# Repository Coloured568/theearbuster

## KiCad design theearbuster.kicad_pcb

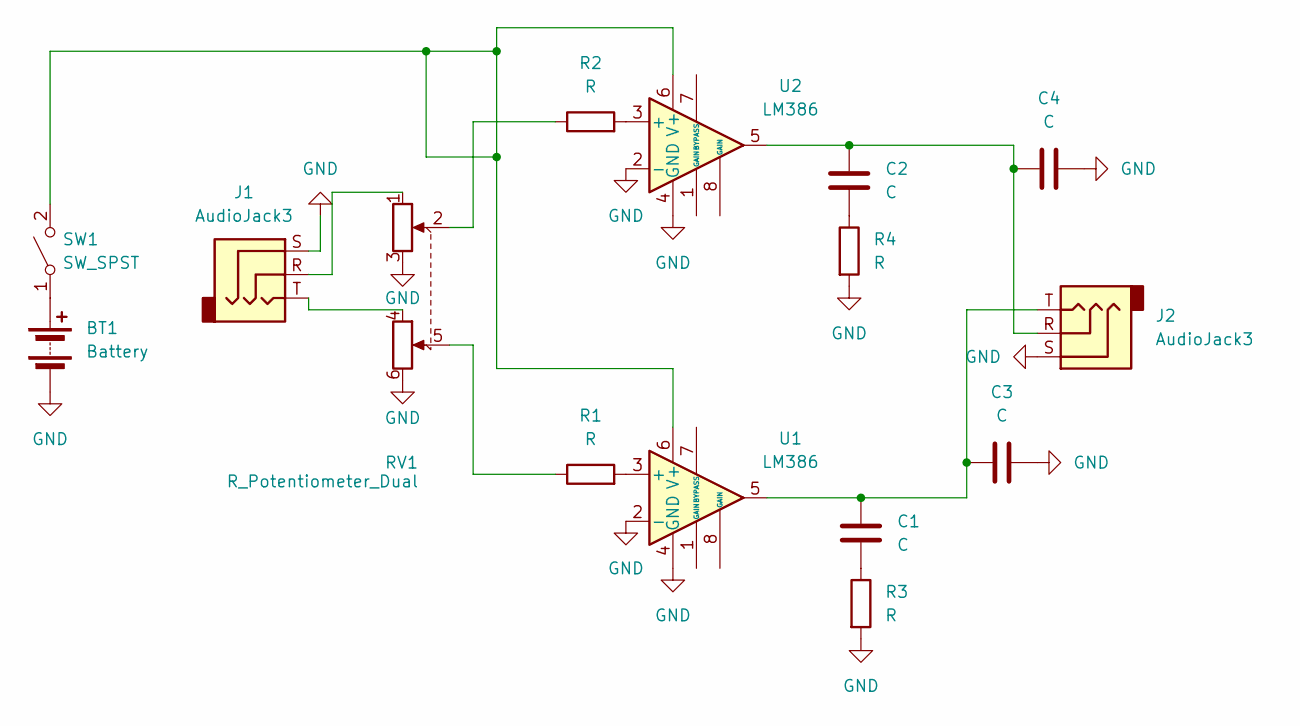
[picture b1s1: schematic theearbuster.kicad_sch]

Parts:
BT1: Battery; BatteryHolder_MPD_BA9VPC_1xPP3
C1, C2: C; C_Rect_L9.0mm_W6.7mm_P7.50mm_MKT
C3, C4: C; CP_Axial_L21.0mm_D8.0mm_P28.00mm_Horizontal
J1, J2: AudioJack3; Jack_3.5mm_PJ320D_Horizontal
R1, R2, R3, R4: R; R_Axial_DIN0204_L3.6mm_D1.6mm_P1.90mm_Vertical
RV1: R_Potentiometer_Dual; Potentiometer_Bourns_PTV112-4_Dual_Vertical
SW1: SW_SPST; SW_DIP_SPSTx01_Slide_6.7x4.1mm_W7.62mm_P2.54mm_LowProfile
U1, U2: LM386; DIP-8_W7.62mm

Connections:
GND: BT1.2 (-), C3.1, C4.1, J1.S, J2.S, R3.2, R4.2, RV1.3, RV1.6, U1.2 (-), U1.4 (GND), U2.2 (-), U2.4 (GND)
unnamed: BT1.1 (+), SW1.1 (A)
unnamed: C1.1, C3.2, J2.T, U1.5
unnamed: C1.2, R3.1
unnamed: C2.1, C4.2, J2.R, U2.5
unnamed: C2.2, R4.1
unnamed: J1.R, RV1.1
unnamed: J1.T, RV1.4
unnamed: R1.1, RV1.5
unnamed: R2.1, RV1.2
unnamed: SW1.2 (B), U1.6 (V+), U2.6 (V+)
unnamed: R1.2, U1.3 (+)
unnamed: R2.2, U2.3 (+)

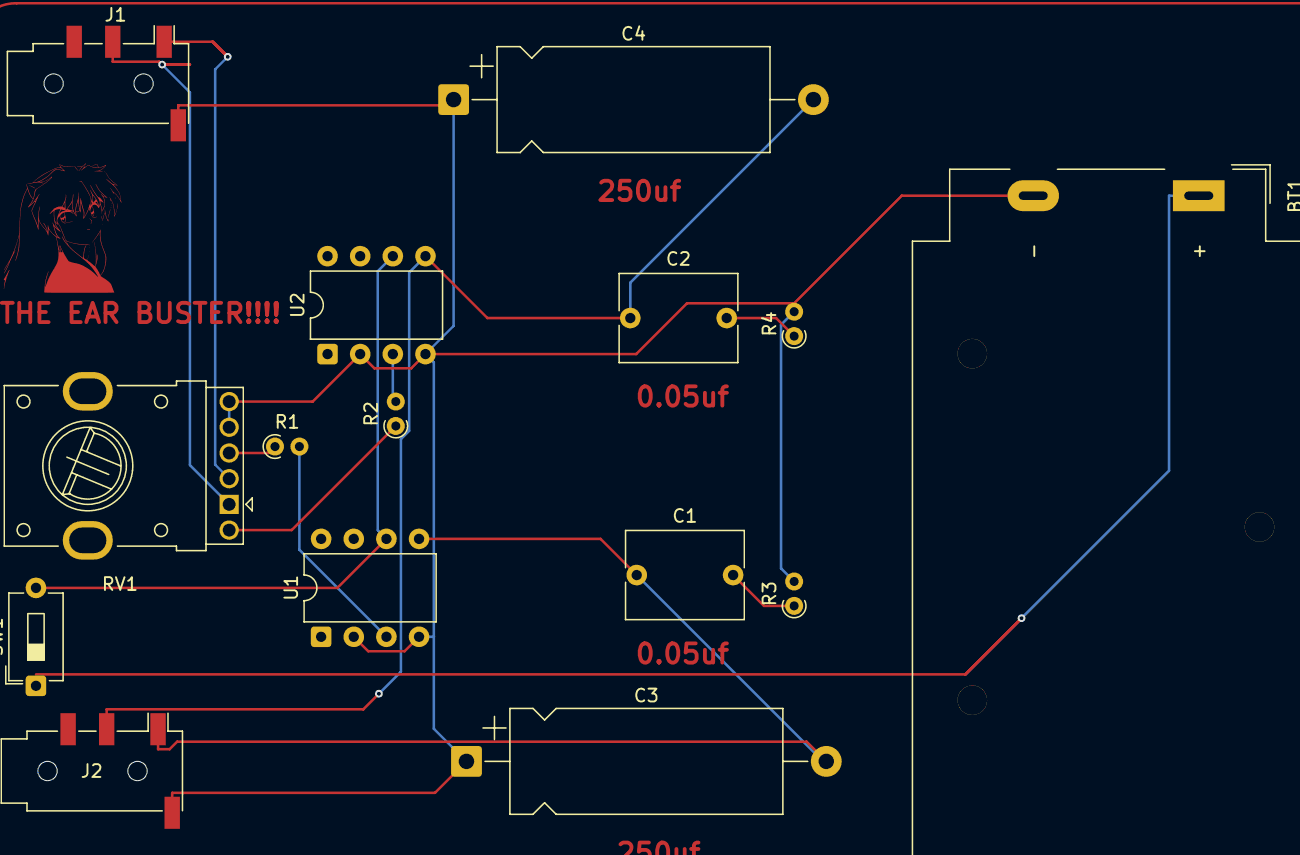
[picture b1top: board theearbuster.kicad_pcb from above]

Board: 2 copper layers, 15 parts (0 on the bottom side), 13 nets.

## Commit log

2026-01-22 Add project description and image to README
2026-01-22 Update image in README for headphone amp project
2026-01-26 Add additional images to README
